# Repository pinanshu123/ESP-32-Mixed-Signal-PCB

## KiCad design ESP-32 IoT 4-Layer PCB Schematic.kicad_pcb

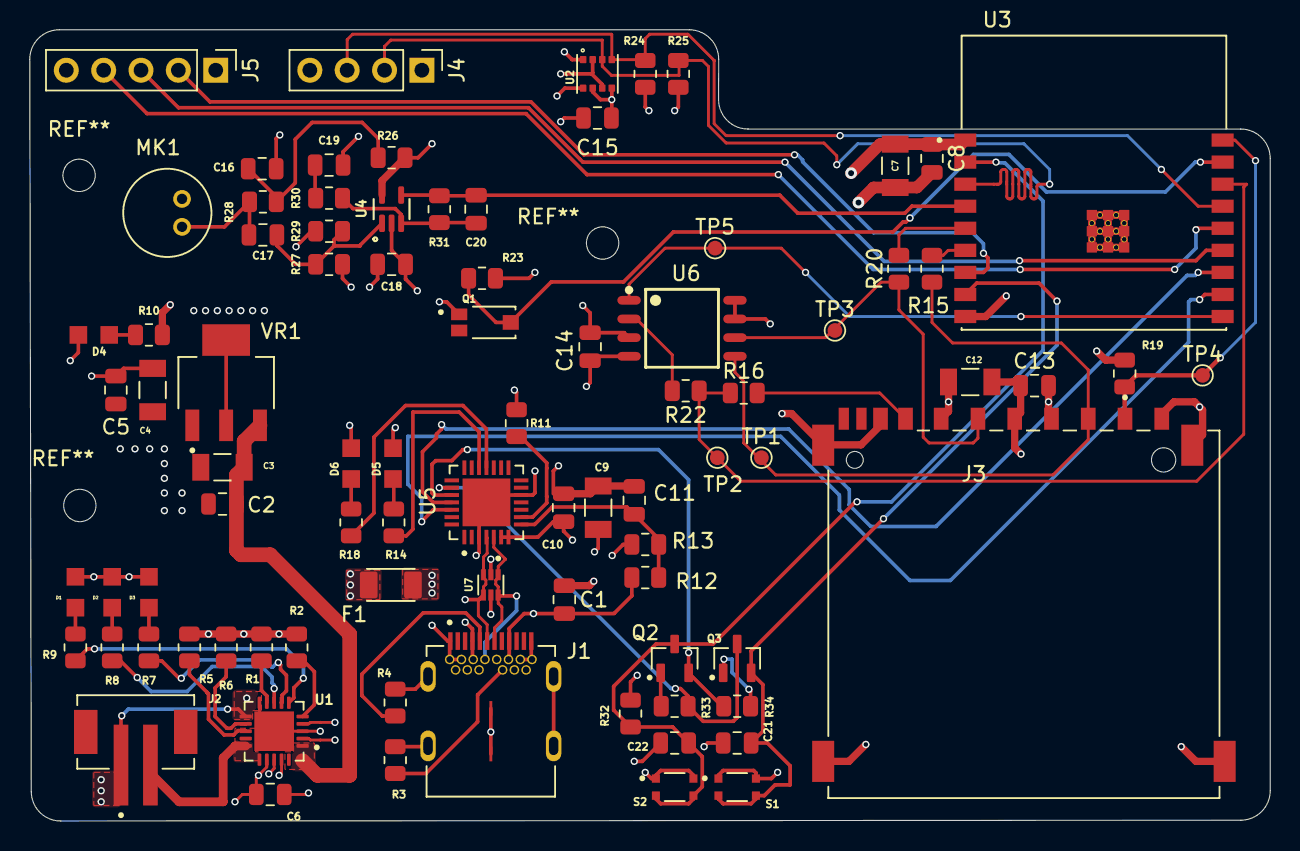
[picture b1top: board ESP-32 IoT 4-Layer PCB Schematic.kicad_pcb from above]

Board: 4 copper layers, 84.4 x 53.8 mm, 85 parts (0 on the bottom side), 55 nets.

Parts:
C1, C2, C5, C8, C10, C13, C14, C15, C16, C18, C20, C21: 0.1u; C_0805_2012Metric
C3, C4, C7, C12: 10u; T491A106K010AT7280
C6, C11, C19, C22: 1u; C_0805_2012Metric
C9: 4.7u; T491A106K010AT7280
C17: 10n; C_0805_2012Metric
D1, D4, D6: LTST-C170KRKT
D2, D5: LTST-C170KGKT
D3: LTST-C170TBKT
F1: 0ZCJ0020FF2E; 0ZCJ0025FF2E
J1: SS-52400-003
J2: B2B-PH-SM4-TB_LF__SN_; JST_B2B-PH-SM4-TB
J3: GSD090012SEU
J4: Conn_01x04_Pin; PinHeader_1x04_P2.54mm_Vertical
J5: Conn_01x05_Pin; PinHeader_1x05_P2.54mm_Vertical
MK1: CMC-5042PF-AC; CUI_CMC-5042PF-AC
Q1: TEMT6000X01
Q2, Q3: BC817
R1, R2, R19, R23, R30, R32, R33, R34: 10k; R_0805_2012Metric
R3, R4: 5k1; R_0805_2012Metric
R5, R26, R28: 2k; R_0805_2012Metric
R6: 20k; R_0805_2012Metric
R7, R8, R9, R10, R14, R18: 470; R_0805_2012Metric
R11: 1k; R_0805_2012Metric
R12: 22k1; R_0805_2012Metric
R13: 47k5; R_0805_2012Metric
R15, R16, R20, R22: 50; R_0805_2012Metric
R24, R25: 4k7; R_0805_2012Metric
R27, R29: 1M; R_0805_2012Metric
R31: 100k; R_0805_2012Metric
S1: BOOT; USLPT2819DT2TR
S2: RESET; USLPT2819DT2TR
TP1: Test MOSI_DI; TestPoint_Pad_D1.0mm
TP2: Test MiSO_DO; TestPoint_Pad_D1.0mm
TP3: Test SCLK; TestPoint_Pad_D1.0mm
TP4: Test CS_SD; TestPoint_Pad_D1.0mm
TP5: Test CS; TestPoint_Pad_D1.0mm
U1: MCP73871-2CCI_ML
U2: BME280
U3: ESP32-C3-WROOM-02-H4
U4: MAX4466EXK
U5: CP2102N-A02-GQFN28
U6: W25Q32JVSSIQ
U7: USBLC6-2SC6; USBLC6-2P6
VR1: LM1117MPX-3.3_NOPB

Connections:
+3.3V: C4.1, C5.1, C7.1, C8.1, C9.1, C10.1, C12.1, C13.1, C14.1, C15.1, C18.1, D4.+, D5.+, D6.+, J3.4 (VDD1), J4.1, J5.1, R11.1, R19.2, R23.1, R24.1, R25.1, R26.1, R27.1, R32.1, U2.2 (CSB), U2.6 (VDDIO), U2.8 (VDD), U3.1 (3V3), U4.5 (VCC), U5.6 (VDD), U5.7 (VREGIN), U6.3 (~WP(IO2)), U6.7 (~HOLD/~RESET(IO3)), U6.8 (VCC), VR1.2 (VOUT_2), VR1.4 (VOUT_4)
+5V: C2.1, C3.1, U1.1 (OUT), VR1.3 (VIN)
/+5V_USB: C6.2, D1.+, D3.+, D3.-, F1.2, R7.2, U1.2 (VPCC), U1.4 (PROG2), U1.17 (CE), U1.18 (IN)
/ESP32-C3-02/BOOT: C21.1, Q3.2, S1.3, S1.4, U3.8 (IO9)
/ESP32-C3-02/CS: TP5.1, U3.10 (IO10), U6.1 (~CS)
/ESP32-C3-02/CS_SD: J3.1 (CD/DAT3), R19.1, TP4.1, U3.18 (IO0)
/ESP32-C3-02/DTR: Q3.3, R33.1, U5.23 (CTS)
/ESP32-C3-02/EN: C22.1, Q2.3, R32.2, S2.3, S2.4, U3.2 (EN)
/ESP32-C3-02/GPIO8: J5.2, U3.7 (IO8)
/ESP32-C3-02/GPIO18: J5.3, U3.13 (IO18)
/ESP32-C3-02/GPIO19: J5.4, U3.14 (IO19)
/ESP32-C3-02/MOSI_DI: J3.2 (CMD), R15.2, TP1.1, U6.5 (DI(IO0))
/ESP32-C3-02/MiC_OUT: C20.2, R31.2, U3.4 (IO5), U4.4 (OUT)
/ESP32-C3-02/MiSO_DO: R16.2, R22.1, TP2.1, U3.16 (IO2)
/ESP32-C3-02/Net-(LED5-K): D5.-, R14.2
/ESP32-C3-02/Net-(LED6-K): D6.-, R18.2
/ESP32-C3-02/PHOTO_C: Q1.3, R23.2, U3.17 (IO1)
/ESP32-C3-02/RTS: Q2.2, R34.1, U5.24 (RTS)
/ESP32-C3-02/RX_TX: U3.12 (TXD), U5.25 (RXD)
/ESP32-C3-02/SCL: J4.3, R24.2, U2.4 (SCK), U3.15 (IO3)
/ESP32-C3-02/SCLK: J3.5 (CLK), R20.1, TP3.1, U6.6 (CLK)
/ESP32-C3-02/SDA: J4.2, R25.2, U2.3 (SDI), U3.3 (IO4)
/ESP32-C3-02/TX_RX: U3.11 (RXD), U5.26 (TXD)
/Net-(LED2-K): D2.-, R8.2
/Net-(LED3-K): D1.-, R9.2
/PWD_LED: D4.-, R10.2
/USB_DN: J1.A7 (DN1), J1.B7 (DN2), U5.5 (D-), U7.1 (I/O1), U7.6 (I/O1)
/USB_DP: J1.A6 (DP1), J1.B6 (DP2), U5.4 (D+), U7.3 (I/O2), U7.4 (I/O2)
/VBAT: J2.2, U1.15 (VBAT), U1.16 (VBAT_SENSE)
/VBUS: C1.1, F1.1, J1.A4 (VBUSA1), J1.A9 (VBUSA2), J1.B4 (VBUSB1), J1.B9 (VBUSB2), R12.1, U7.5 (VBUS)
GND: C1.2, C2.2, C3.2, C4.2, C5.2, C6.1, C7.2, C8.2, C9.2, C10.2, C11.2, C12.2, C13.2, C14.2, C15.2, C16.1, C18.2, C19.2, C21.2, C22.2, J1.A1 (GNDA1), J1.A12 (GNDA2), J1.B1 (GNDB1), J1.B12 (GNDB2), J1.G1 (GND/SHIELD), J1.G2 (GND/SHIELD__1), J1.G3 (GND/SHIELD__2), J1.G4 (GND/SHIELD__3), J1.S1 (GND/SHIELD__4), J1.S2 (GND/SHIELD__5), J1.S3 (GND/SHIELD__6), J1.S4 (GND/SHIELD__7), J2.1, J3.3 (VSS1), J3.6 (VSS2), J3.8 (DAT1), J3.9 (DAT2), J3.G1 (SHIELD_GND), J3.G2 (SHIELD_GND__1), J3.G3 (SHIELD_GND__2), J3.G4 (SHIELD_GND__3), J4.4, J5.5, MK1.GND, Q1.1, R1.1, R2.1, R3.2, R4.2, R5.1, R6.1, R10.1, R13.2, R29.2, S1.1, S1.2, S2.1, S2.2, U1.3 (SEL), U1.11 (VSS), U2.1 (GND), U2.5 (SDO), U2.7 (GND__1), U3.9 (GND), U3.19 (GND__1), U3.20 (GND__2), U3.21 (GND__3), U3.22 (GND__4), U3.23 (GND__5), U3.24 (GND__6), U3.25 (GND__7), U3.26 (GND__8), U3.27 (GND__9), U3.28 (GND__10), U3.29 (GND__11), U3.30 (GND__12), U3.31 (GND__13), U3.32 (GND__14), U3.33 (GND__15), U3.34 (GND__16), U3.35 (GND__17), U3.36 (GND__18), U3.37 (GND__19), U3.38 (GND__20), U3.39 (GND__21), U4.2 (GND), U5.3 (GND), U5.12 (SUSPEND), U5.29 (GND__1), U6.4 (GND), U7.2 (GND), VR1.1 (GND)
unnamed: C16.2, R26.2, R28.1
unnamed: C17.1, MK1.OUT, R28.2
unnamed: C19.1, R30.2
unnamed: J1.A5 (CC1), R4.1
unnamed: J1.B5 (CC2), R3.1
unnamed: J3.7 (DAT0), R16.1
unnamed: Q2.1, R33.2
unnamed: Q3.1, R34.2
unnamed: R5.2, U1.13 (PROG1)
unnamed: R6.2, U1.12 (PROG3)
unnamed: R8.1, U1.8 (STAT1/*LBO)
unnamed: R7.1, U1.7 (STAT2)
unnamed: R2.2, U1.5 (THERM)
unnamed: R9.1, U1.6 (~PG)
unnamed: R1.2, U1.9 (~TE)
unnamed: R20.2, U3.5 (IO6)
unnamed: R15.1, U3.6 (IO7)
unnamed: C17.2, R27.2, R29.1, U4.1 (IN+)
unnamed: C20.1, R30.1, R31.1, U4.3 (IN-)
unnamed: R14.1, U5.19 (GPIO.0/TXT)
unnamed: R18.1, U5.18 (GPIO.1/RXT)
unnamed: C11.1, R12.2, R13.1, U5.8 (VBUS)
unnamed: R11.2, U5.9 (~RST)
unnamed: R22.2, U6.2 (DO(IO1))
